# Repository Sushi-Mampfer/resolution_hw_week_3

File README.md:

# The perfect alarm
A semi configurable alarm, you can set times from 1-15 hours. It's perfect, because it'll definitely make you wake up early.

It works by using a 4060 that triggers a 4020 on it's final output, since the 4020 is triggered on the falling edge it continues perfectly. And the last 4 outputs of the 4020 are 1/2/4/8 hour(s) (although an hour is a bit less than 58 minutes, because I couldn't use exact values). The buzzers signal is grounded by 4 different switches which are grounded by the 1/2/4/8 hour(s) pins. This allows you to put in any number from 1 to 15 hours. The reset switch grounds the buzzers input and powers the RESET pin on the 4060 and 4020.

---
## Schematic

## PCB

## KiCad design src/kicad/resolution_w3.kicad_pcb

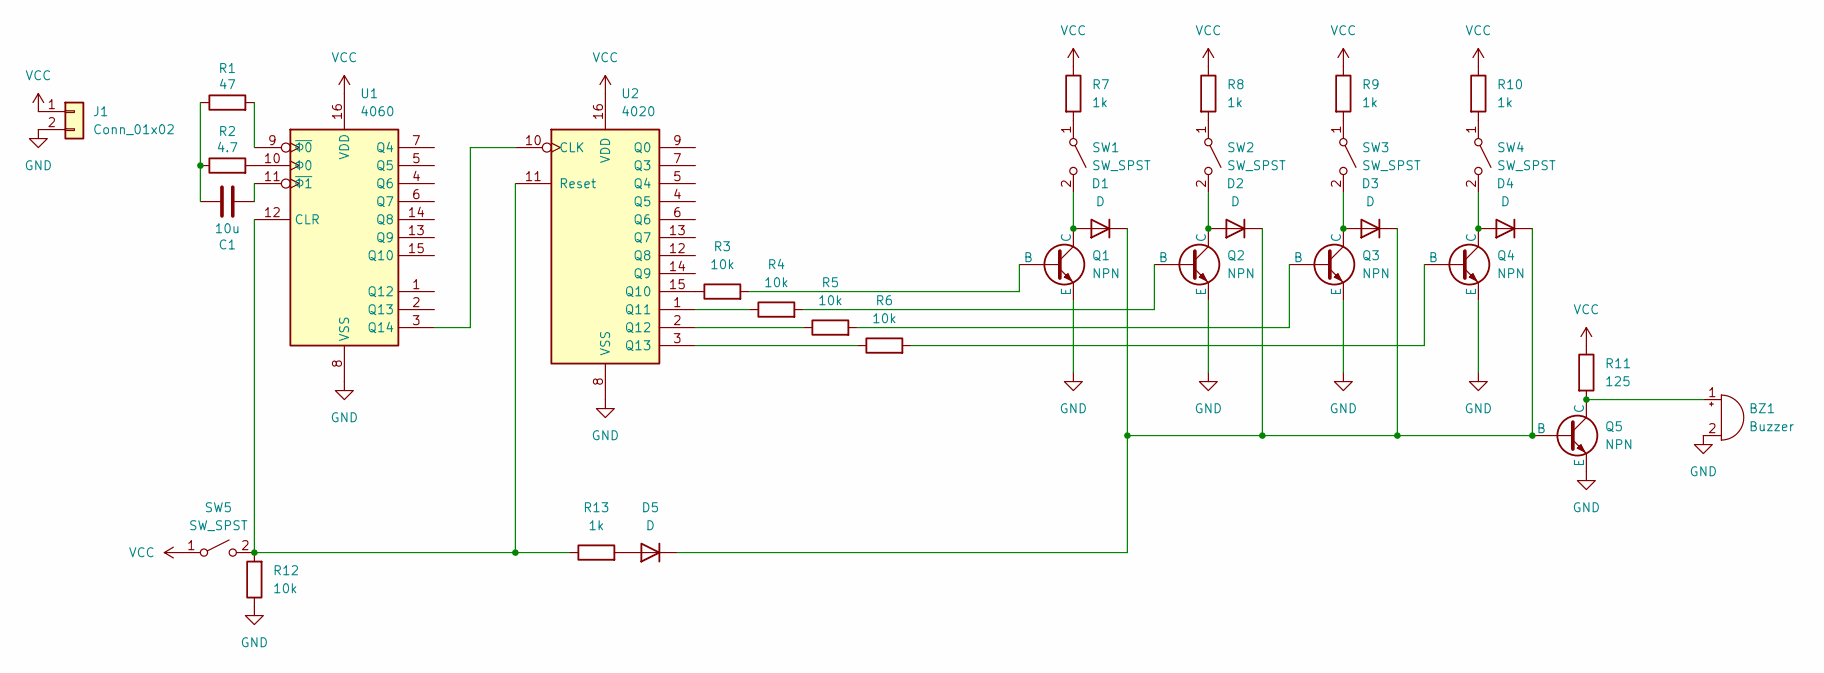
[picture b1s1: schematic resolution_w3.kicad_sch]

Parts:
BZ1: Buzzer; Buzzer_12x9.5RM7.6
C1: 10u; C_Disc_D5.0mm_W2.5mm_P5.00mm
D1, D2, D3, D4, D5: D; D_DO-35_SOD27_P7.62mm_Horizontal
J1: Conn_01x02; PinHeader_1x02_P2.54mm_Vertical
Q1, Q2, Q3, Q4, Q5: NPN; TO-92L_Inline_Wide
R1: 47; R_Axial_DIN0204_L3.6mm_D1.6mm_P7.62mm_Horizontal
R2: 4.7; R_Axial_DIN0204_L3.6mm_D1.6mm_P7.62mm_Horizontal
R3, R4, R5, R6, R12: 10k; R_Axial_DIN0204_L3.6mm_D1.6mm_P7.62mm_Horizontal
R7, R8, R9, R10, R13: 1k; R_Axial_DIN0204_L3.6mm_D1.6mm_P7.62mm_Horizontal
R11: 125; R_Axial_DIN0204_L3.6mm_D1.6mm_P7.62mm_Horizontal
SW1, SW2, SW3, SW4, SW5: SW_SPST; SW_PUSH_6mm
U1: 4060; DIP-16_W7.62mm
U2: 4020; DIP-16_W7.62mm

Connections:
GND: BZ1.2 (-), J1.2, Q1.3 (E), Q2.3 (E), Q3.3 (E), Q4.3 (E), Q5.3 (E), R12.1, U1.8 (VSS), U2.8 (VSS)
unnamed: BZ1.1 (+), Q5.1 (C), R11.2
unnamed: C1.1, R1.1, R2.1
unnamed: D1.2 (A), Q1.1 (C), SW1.2 (B)
unnamed: D1.1 (K), D2.1 (K), D3.1 (K), D4.1 (K), D5.1 (K), Q5.2 (B)
unnamed: D2.2 (A), Q2.1 (C), SW2.2 (B)
unnamed: D3.2 (A), Q3.1 (C), SW3.2 (B)
unnamed: D4.2 (A), Q4.1 (C), SW4.2 (B)
unnamed: D5.2 (A), R13.2
unnamed: Q1.2 (B), R3.2
unnamed: Q2.2 (B), R4.2
unnamed: Q3.2 (B), R5.2
unnamed: Q4.2 (B), R6.2
unnamed: R7.2, SW1.1 (A)
unnamed: R8.2, SW2.1 (A)
unnamed: R9.2, SW3.1 (A)
unnamed: R10.2, SW4.1 (A)
unnamed: R12.2, R13.1, SW5.2 (B), U1.12 (CLR), U2.11 (Reset)
unnamed: U1.3 (Q14), U2.10 (CLK)
unnamed: R1.2, U1.9 (~Φ0)
unnamed: C1.2, U1.11 (~Φ1)
unnamed: R2.2, U1.10 (Φ0)
unnamed: R3.1, U2.15 (Q10)
unnamed: R4.1, U2.1 (Q11)
unnamed: R5.1, U2.2 (Q12)
unnamed: R6.1, U2.3 (Q13)
VCC: J1.1, R7.1, R8.1, R9.1, R10.1, R11.1, SW5.1 (A), U1.16 (VDD), U2.16 (VDD)

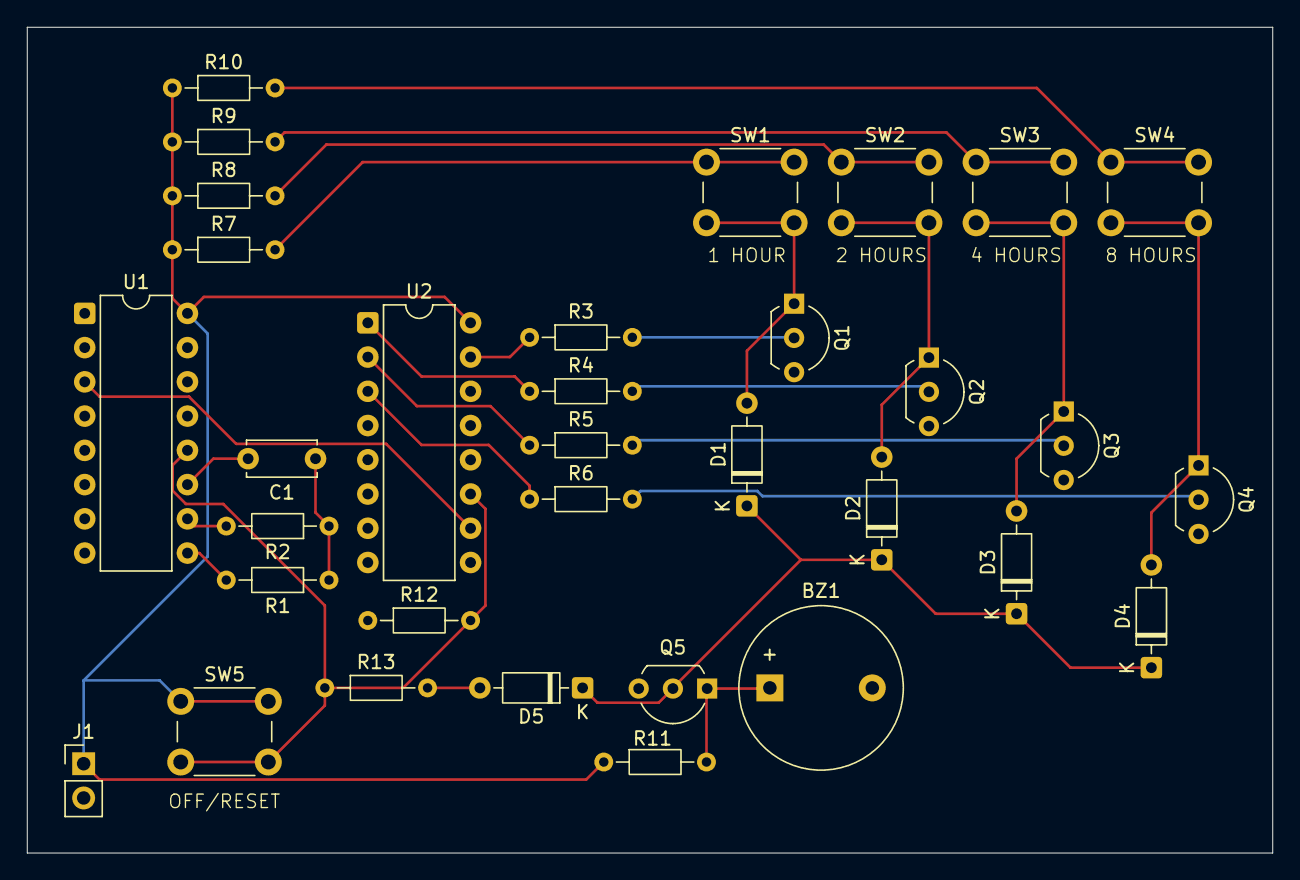
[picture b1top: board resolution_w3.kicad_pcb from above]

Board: 2 copper layers, 92.4 x 61.3 mm, 33 parts (0 on the bottom side), 27 nets.

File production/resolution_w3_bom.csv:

Designator,Footprint,Quantity,Value,LCSC Part #
BZ1,Buzzer_12x9.5RM7.6,1,Buzzer,
C1,C_Disc_D5.0mm_W2.5mm_P5.00mm,1,10u,
"D1, D2, D3, D4, D5",D_DO-35_SOD27_P7.62mm_Horizontal,5,D,
J1,PinHeader_1x02_P2.54mm_Vertical,1,Conn_01x02,
"Q1, Q2, Q3, Q4, Q5",TO-92L_Inline_Wide,5,NPN,
R1,R_Axial_DIN0204_L3.6mm_D1.6mm_P7.62mm_Horizontal,1,47,
"R10, R13, R7, R8, R9",R_Axial_DIN0204_L3.6mm_D1.6mm_P7.62mm_Horizontal,5,1k,
R11,R_Axial_DIN0204_L3.6mm_D1.6mm_P7.62mm_Horizontal,1,125,
"R12, R3, R4, R5, R6",R_Axial_DIN0204_L3.6mm_D1.6mm_P7.62mm_Horizontal,5,10k,
R2,R_Axial_DIN0204_L3.6mm_D1.6mm_P7.62mm_Horizontal,1,4.7,
"SW1, SW2, SW3, SW4, SW5",SW_PUSH_6mm,5,SW_SPST,
U1,DIP-16_W7.62mm,1,4060,
U2,DIP-16_W7.62mm,1,4020,

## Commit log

2026-04-09 Added journal
2026-04-09 added nor test
2026-04-09 Added kicad dir
2026-04-09 Kicad files
2026-04-09 creaded production dir
2026-04-09 Added production files
2026-04-09 Readme
2026-04-09 Added my IC docs
